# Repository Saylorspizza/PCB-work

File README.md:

# PCB-work
First PCB designs
Taking the first steps to learning PCB design.  Will be uploading all the versions of the PCB to rollback if needed as well as get feedback when shared.

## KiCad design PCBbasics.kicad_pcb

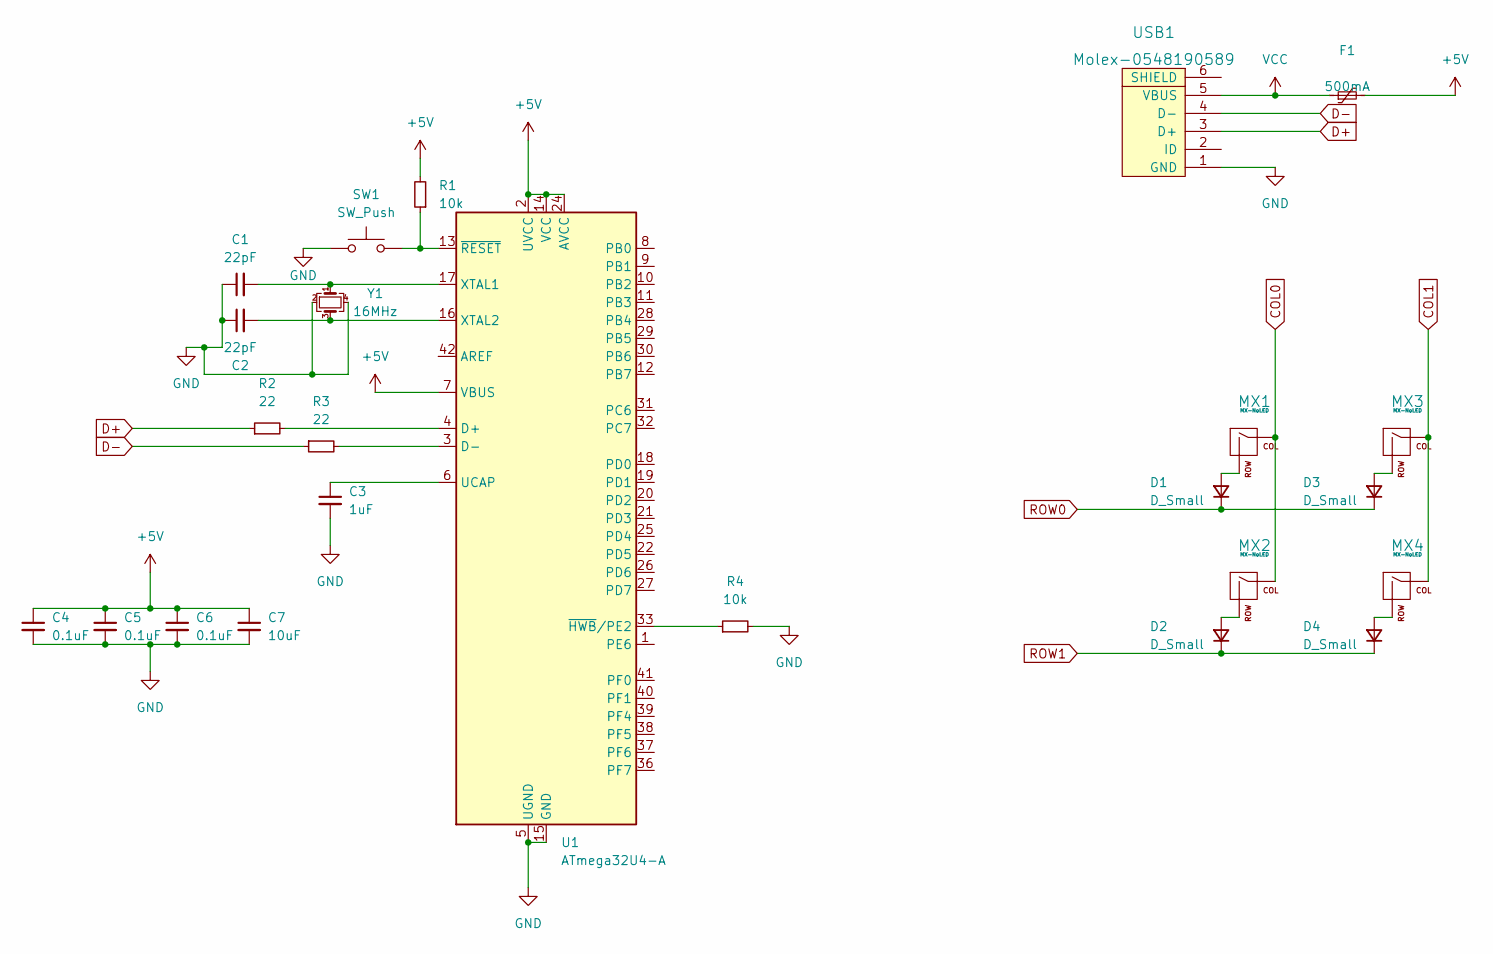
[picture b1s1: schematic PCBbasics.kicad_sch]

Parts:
C1, C2: 22pF; C_0805_2012Metric
C3: 1uF; C_0805_2012Metric
C4, C5, C6: 0.1uF; C_0805_2012Metric
C7: 10uF; C_0805_2012Metric
D1, D2, D3, D4: D_Small; D_SOD-123
F1: 500mA; Fuse_1206_3216Metric
MX1, MX2, MX3, MX4: MX-NoLED; MX-1U-NoLED
R1, R4: 10k; R_0805_2012Metric_Pad1.20x1.40mm_HandSolder
R2, R3: 22; R_0805_2012Metric_Pad1.20x1.40mm_HandSolder
SW1: SW_Push; SKQG-1155865
U1: ATmega32U4-A; TQFP-44_10x10mm_P0.8mm
USB1: Molex-0548190589
Y1: 16MHz; Crystal_SMD_3225-4Pin_3.2x2.5mm

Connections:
+5V: C4.1, C5.1, C6.1, C7.1, F1.2, R1.2, U1.2 (UVCC), U1.7 (VBUS), U1.14 (VCC), U1.24 (AVCC), U1.34 (VCC), U1.44 (AVCC)
COL0: MX1.1 (COL), MX2.1 (COL)
COL1: MX3.1 (COL), MX4.1 (COL)
D+: R2.1, USB1.3 (D+)
D-: R3.1, USB1.4 (D-)
GND: C1.1, C2.1, C3.2, C4.2, C5.2, C6.2, C7.2, R4.2, SW1.1, U1.5 (UGND), U1.15 (GND), U1.23 (GND), U1.35 (GND), U1.43 (GND), USB1.1 (GND), Y1.2, Y1.4
unnamed: C1.2, U1.17 (XTAL1), Y1.1
unnamed: C2.2, U1.16 (XTAL2), Y1.3
unnamed: C3.1, U1.6 (UCAP)
unnamed: D1.2 (A), MX1.2 (ROW)
unnamed: D2.2 (A), MX2.2 (ROW)
unnamed: D3.2 (A), MX3.2 (ROW)
unnamed: D4.2 (A), MX4.2 (ROW)
unnamed: R1.1, SW1.2, U1.13 (~RESET)
unnamed: R2.2, U1.4 (D+)
unnamed: R3.2, U1.3 (D-)
unnamed: R4.1, U1.33 (~HWB/PE2)
ROW0: D1.1 (K), D3.1 (K)
ROW1: D2.1 (K), D4.1 (K)
VCC: F1.1, USB1.5 (VBUS)

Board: 2 copper layers, 24 parts (3 on the bottom side), 20 nets, no tracks yet.

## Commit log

2023-02-22 Base files
2023-02-22 Add submodules
2023-02-22 Changed file locations
2023-02-22 Fixing project directory
2023-02-22 Added footprint libraries
2023-02-22 Starting to place components down and wire
2023-02-27 Completed MCU Area
2023-02-27 Schematic Done - Micro USB Ver.
2023-02-27 Footprints annotated
2023-03-01 PCB Start
2023-03-01 PCB Finished
2023-03-01 Routing start
